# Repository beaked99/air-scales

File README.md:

Seth - everything for the KiCad is in the /hardware page. the project *should* open up at /hardware/air-scales. let me know if it doesnt work for you. At this stage all that is there is a big schematic, and ya... i went outside the fucking page border because i dont know how to update that either. fml. 
Scope of the project is to take an ESP32 run it off 12V vehicle power, read 0-5V air pressure on the ESP32. read ambient air pressure and ambient air temperature. Add GPS sensor if I can to get LAT / LONG. ESP32 should only have a headache rack connecting outside 12V power and the main 0-5V air pressure. 
I haven't decided what air pressure sensor I will use. I might look long and hard at the competitors link you sent me to see what they are using. I dont think I want battery power unlike them, no truck driver wants to hop in their semi and not see the fucking esp32 cause some stupid battery went dead. super easy to hook into trailer light wiring at the very least. we are not pulling a lot of watts here on this whole operation I dont think.

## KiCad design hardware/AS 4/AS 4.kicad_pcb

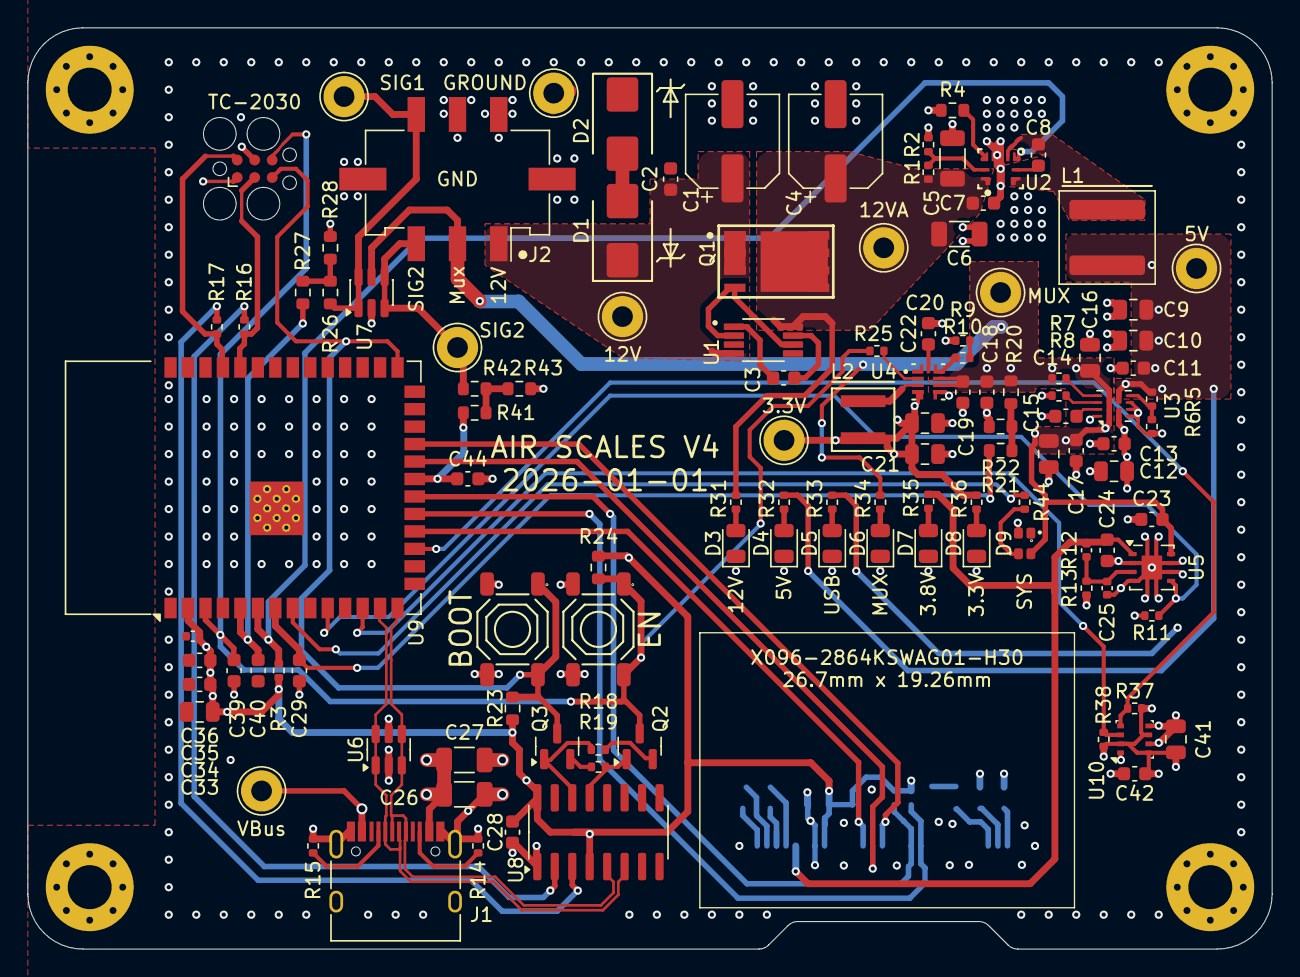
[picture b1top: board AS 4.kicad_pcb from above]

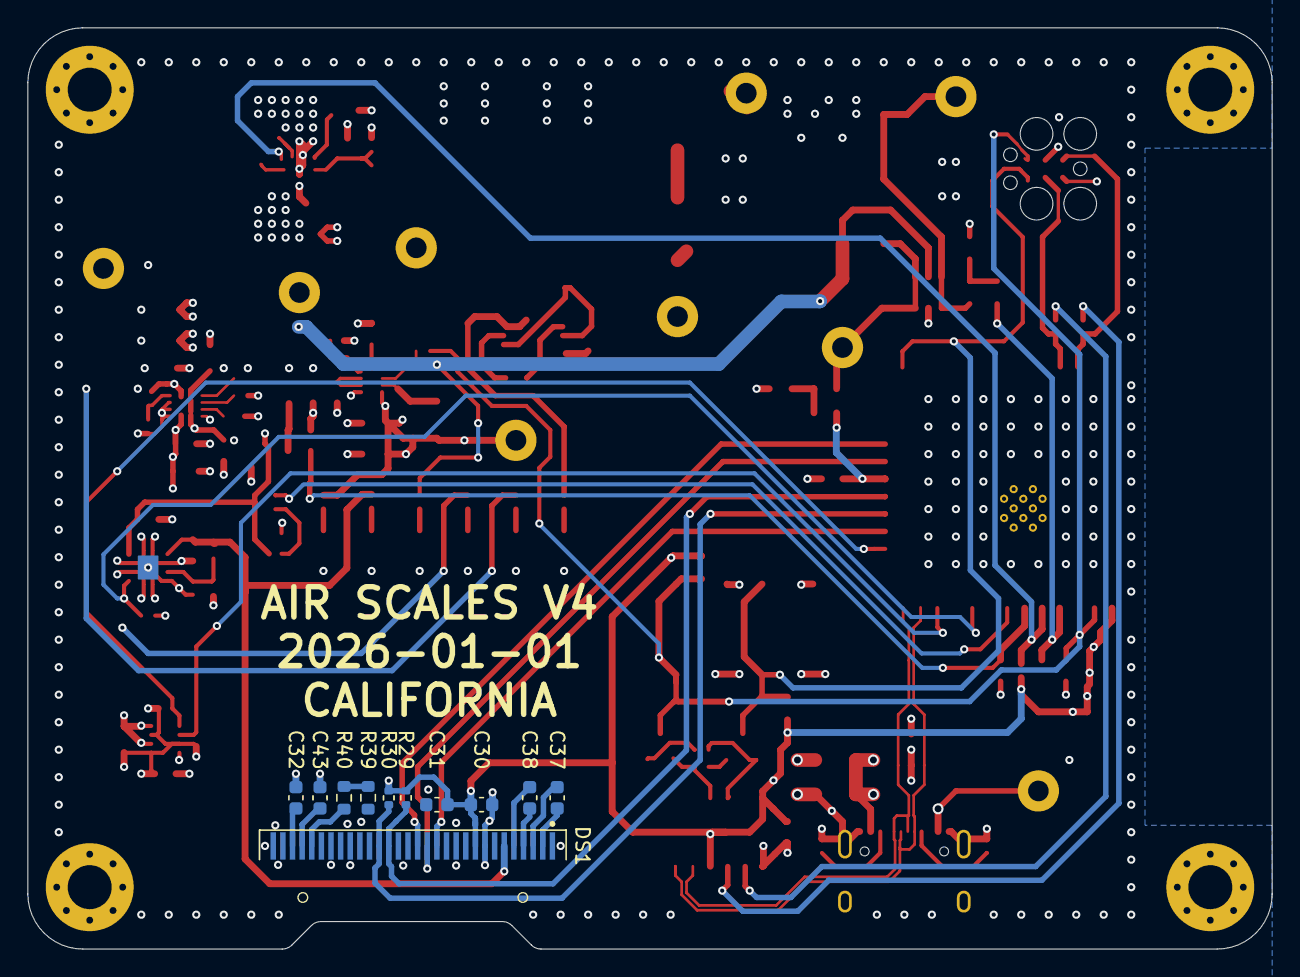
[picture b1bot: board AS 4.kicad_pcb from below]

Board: 4 copper layers, 90.5 x 67.0 mm, 131 parts (11 on the bottom side), 73 nets.

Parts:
C1, C4: 47uF; CP_Elec_6.3x7.7
C2, C7, C8, C11, C13, C14, C17, C18, C19, C28, C29, C30, C31, C34, C35, C37, C38, C40, C42, C44: 100nF; C_0603_1608Metric
C3, C23, C24, C32: 2.2uF; C_0603_1608Metric
C5, C6: 10uF; C_1206_3216Metric
C9, C15, C16, C20, C21: 22uF; C_0805_2012Metric
C10, C12, C33, C41: 10uF; C_0805_2012Metric
C22: 22nF; C_0603_1608Metric
C25, C36: 10nF; C_0402_1005Metric
C26, C27: 22uF; C_1206_3216Metric
C39: 1uF; C_0603_1608Metric
C43: 4.7uF; C_0603_1608Metric
D1: SMBJ28A; D_SMB
D2: SMBJ14A; D_SMB
D3, D4, D5, D6, D7, D8: LED_Small; LED_0805_2012Metric
D9: WS2812B; LED-SMD_4P-L1.6-W1.5_XL-1615RGBC-WS2812B
DS1: OLED-128O064D
H1, H2, H3, H4: MountingHole_Pad; MountingHole_3.2mm_M3_Pad_Via
J1: USB_C_Receptacle_USB2.0_16P; USB_C_Receptacle_HRO_TYPE-C-31-M-12
J2: Conn_02x03_Odd_Even; Molex_Micro-Fit_3.0_43045-0618_2x03-1MP_P3.00mm_Vertical
J3: TC2030-NL; Tag-Connect_TC2030-IDC-FP_2x03_P1.27mm_Vertical
L1: 10uH; L_Coilcraft_XAL6060-XXX
L2: 2.2uH; IND_XGL4020_COC
Q1: IAUC120N06S5L011; INF-PG-TDSON-8-33-V
Q2, Q3: S8050; SOT-23
R1, R11: 100K; R_0402_1005Metric
R2, R10: 15K; R_0402_1005Metric
R3, R5, R7, R13, R18, R19, R25: 10K; R_0402_1005Metric
R4: 82K; R_0603_1608Metric
R6, R29, R30, R31: 4.7K; R_0402_1005Metric
R8: 82K; R_0402_1005Metric
R9: 47K; R_0402_1005Metric
R12: 22K; C_0402_1005Metric
R14, R15: 5.1K; R_0402_1005Metric
R16, R17, R32, R33, R34, R37, R38: 1K; R_0402_1005Metric
R20, R26, R41: 68K; R_0603_1608Metric
R21, R27, R42: 220; R_0603_1608Metric
R22, R23, R24, R28, R43: 100K; R_0603_1608Metric
R35: 500; R_0402_1005Metric
R36, R44: 220; R_0402_1005Metric
R39, R40: 300K; R_0603_1608Metric
S1, S2: Tactile Button, 160gf; SW-SMD_4P-L5.1-W5.1-P3.70-LS6.5-TL-2
TP1, TP2, TP3, TP4, TP5, TP6, TP7, TP8, TP9: TestPoint_Probe; TestPoint_THTPad_D3.0mm_Drill1.5mm
U1: LM74610QDGKTQ1; SOP65P490X110-8N
U2: LMR604205SRAKRQ1; RAK0009A-MFG
U3: TPS2121RUXR; Texas_VQFN-HR-12_2x2.5mm_P0.5mm
U4: TPS62901Q1; VQFNHR9_RYT_TEX
U5: TPS73501DRBR; Texas_DRB0008A
U6, U7: USBLC6-2SC6; SOT-23-6
U8: CH340C; SOP-16_3.9x9.9mm_P1.27mm
U9: ESP32-S3-WROOM-1
U10: BME280; Bosch_LGA-8_2.5x2.5mm_P0.65mm_ClockwisePinNumbering

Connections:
+3.3V: C20.1, C21.1, C28.1, C30.1, C31.1, C33.1, C34.1, C35.1, C36.1, C41.1, C42.1, DS1.9 (VDD), L2.2, R3.2, R23.2, R24.2, R29.1, R30.1, R36.1, R37.1, R38.1, TP5.1, U4.3 (VOS), U8.4 (V3), U8.16 (VCC), U9.2 (3V3), U10.2 (CSB), U10.6 (VDDIO), U10.8 (VDD)
+3.8V: C24.1, DS1.6 (VBAT), R12.1, R35.1, U5.1 (OUT)
+5V: C9.1, C10.1, C11.1, L1.2, R5.2, R32.1, TP3.1, U3.7 (IN1)
+5VBus: C12.1, C13.1, C26.1, C27.1, J1.A4 (VBUS), J1.A9 (VBUS), J1.B4 (VBUS), J1.B9 (VBUS), J3.1 (VCC), R33.1, TP6.1, U3.2 (IN2), U6.5 (VBUS)
+5VMUX: C15.1, C16.1, C17.1, C18.1, C19.1, C23.1, D9.2 (VDD), J2.2, R7.2, R20.2, R34.1, TP4.1, U3.1 (OUT), U3.8 (OUT__2), U4.5 (EN), U4.6 (VIN), U5.8 (IN), U7.5 (VBUS)
+12V: C1.1, C2.1, D1.1, J2.1, Q1.1 (SOURCE), Q1.2 (SOURCE), Q1.3 (SOURCE), TP1.1, U1.4 (ANODE)
+12VA: C4.1, C5.1, C6.1, C7.1, Q1.5 (DRAIN), Q1.6 (DRAIN), Q1.7 (DRAIN), Q1.8 (DRAIN), R1.1, R31.1, TP2.1, U1.8 (CATHODE), U2.1 (VIN)
/3.8VEN: R11.1, U5.5 (EN), U9.10 (IO17)
/5VNet: C8.2, L1.1, U2.3 (SW), U2.6 (FB)
/5VPG: R3.1, U2.5 (PG), U9.6 (IO6)
/5V_MUX_GPIO: C29.1, R21.1, U9.7 (IO7)
/BOOT: J3.5 (RST), Q3.3 (C), R23.1, S2.1 (A), S2.2 (B), U9.27 (IO0)
/CS: DS1.13 (~CS), U9.18 (IO10)
/D/C: DS1.15 (D/~C), U9.23 (IO21)
/EN: C39.1, J3.6 (BOOT), Q2.3 (C), R24.1, R25.1, S1.1 (A), S1.2 (B), U9.3 (EN)
/GATE: Q1.4 (GATE), U1.2 (GATEPULLDOWN), U1.6 (GATEDRIVE)
/LED: R44.1, U9.8 (IO15)
/MIP_1: J2.6, R26.2, TP8.1, U7.1 (I/O1), U7.6 (I/O1)
/MIP_2: J2.3, R41.2, TP9.1, U7.3 (I/O2), U7.4 (I/O2)
/PG: R25.2, U4.1 (PG)
/RES: DS1.14 (~RES), U9.22 (IO14)
/RXD0: J3.3 (RX), R16.1, U9.36 (RXD0)
/SCL: R37.2, U9.17 (IO9), U10.4 (SCK)
/SCLK: DS1.18 (D0), R29.2, U9.20 (IO12)
/SDA: R38.2, U9.12 (IO8), U10.3 (SDI)
/SDIN: DS1.19 (D1), R30.2, U9.19 (IO11)
/SIG_1: C40.1, R27.1, U9.5 (IO5)
/SIG_2: C44.1, R42.1, U9.21 (IO13)
/TXD0: J3.2 (TX), R17.1, U9.37 (TXD0)
/USB_D+: J1.A6 (D+), J1.B6 (D+), U6.3 (I/O2), U6.4 (I/O2), U8.5 (UD+), U9.14 (USB_D+)
/USB_D-: J1.A7 (D-), J1.B7 (D-), U6.1 (I/O1), U6.6 (I/O1), U8.6 (UD-), U9.13 (USB_D-)
GND: C1.2, C2.2, C4.2, C5.2, C6.2, C7.2, C9.2, C10.2, C11.2, C12.2, C13.2, C14.2, C15.2, C16.2, C17.2, C18.2, C19.2, C20.2, C21.2, C22.2, C23.2, C24.2, C25.2, C26.2, C27.2, C28.2, C29.2, C30.2, C31.2, C32.2, C33.2, C34.2, C35.2, C36.2, C39.2, C40.2, C41.2, C42.2, C43.1, C44.2, D2.1, D3.1 (K), D4.1 (K), D5.1 (K), D6.1 (K), D7.1 (K), D8.1 (K), D9.3 (GND), DS1.1 (GND), DS1.8 (VSS), DS1.10 (BS0), DS1.11 (BS1), DS1.12 (BS2), DS1.16 (R/~W), DS1.17 (E/~RD), DS1.21 (D3), DS1.22 (D4), DS1.23 (D5), DS1.24 (D6), DS1.25 (D7), DS1.29 (VLSS), DS1.30 (GND), H1.1, H2.1, H3.1, H4.1, J1.A1 (GND), J1.A12 (GND), J1.B1 (GND), J1.B12 (GND), J1.S1 (SHIELD), J2.4, J2.5, J2.MP (MountPin), J3.4 (GND), R2.2, R4.2, R6.1, R8.2, R10.2, R11.2, R13.2, R14.2, R15.2, R22.1, R28.1, R39.1, R43.1, S1.3 (C), S1.4 (D), S2.3 (C), S2.4 (D), TP7.1, U2.2 (PGND), U2.7 (MODE_SYNC), U3.3 (CP2), U3.4 (OV2), U3.5 (OV1), U3.12 (GND), U4.4 (GND), U5.2 (NC_1), U5.4 (GND), U5.6 (NC_2), U5.7 (NC_3), U5.9 (EP_1), U6.2 (GND), U7.2 (GND), U8.1 (GND), U9.1 (GND), U9.40 (GND), U9.41 (GND), U10.1 (GND), U10.5 (SDO), U10.7 (GND)
unnamed: D1.2, D2.2
unnamed: D3.2 (A), R31.2
unnamed: D4.2 (A), R32.2
unnamed: D5.2 (A), R33.2
unnamed: D6.2 (A), R34.2
unnamed: D7.2 (A), R35.2
unnamed: D8.2 (A), R36.2
unnamed: D9.4 (DIN), R44.2
unnamed: C38.2, DS1.5 (C1N)
unnamed: C38.1, DS1.4 (C1P)
unnamed: C37.1, DS1.2 (C2N)
unnamed: C37.2, DS1.3 (C2P)
unnamed: DS1.26 (IREF), R40.2
unnamed: C32.1, DS1.28 (VCC)
unnamed: C43.2, DS1.27 (VCOMH)
unnamed: J1.A5 (CC1), R15.1
unnamed: J1.B5 (CC2), R14.1
unnamed: Q2.2 (B), R18.1
unnamed: Q2.1 (E), R19.2, U8.13 (~DTR)
unnamed: Q3.2 (B), R19.1
unnamed: Q3.1 (E), R18.2, U8.14 (~RTS)
unnamed: R9.2, R10.1
unnamed: R20.1, R21.2, R22.2
unnamed: R26.1, R27.2, R28.2
unnamed: R39.2, R40.1
unnamed: R41.1, R42.2, R43.2
unnamed: C3.1, U1.7 (VCAPH)
unnamed: C3.2, U1.1 (VCAPL)
unnamed: C8.1, U2.4 (BOOT)
unnamed: R1.2, R2.1, U2.9 (EN)
unnamed: R4.1, U2.8 (RT)
unnamed: R8.1, U3.10 (ILIM)
unnamed: R5.1, R6.2, U3.6 (PR1)
unnamed: C14.1, U3.11 (SS)
unnamed: R7.1, U3.9 (ST)
unnamed: R9.1, U4.7 (MODE/S-CONF)
unnamed: C22.1, U4.8 (SS/TR)
unnamed: L2.1, U4.2 (SW)
unnamed: C25.1, R12.2, R13.1, U5.3 (FBNR)
unnamed: R17.2, U8.3 (RXD)
unnamed: R16.2, U8.2 (TXD)

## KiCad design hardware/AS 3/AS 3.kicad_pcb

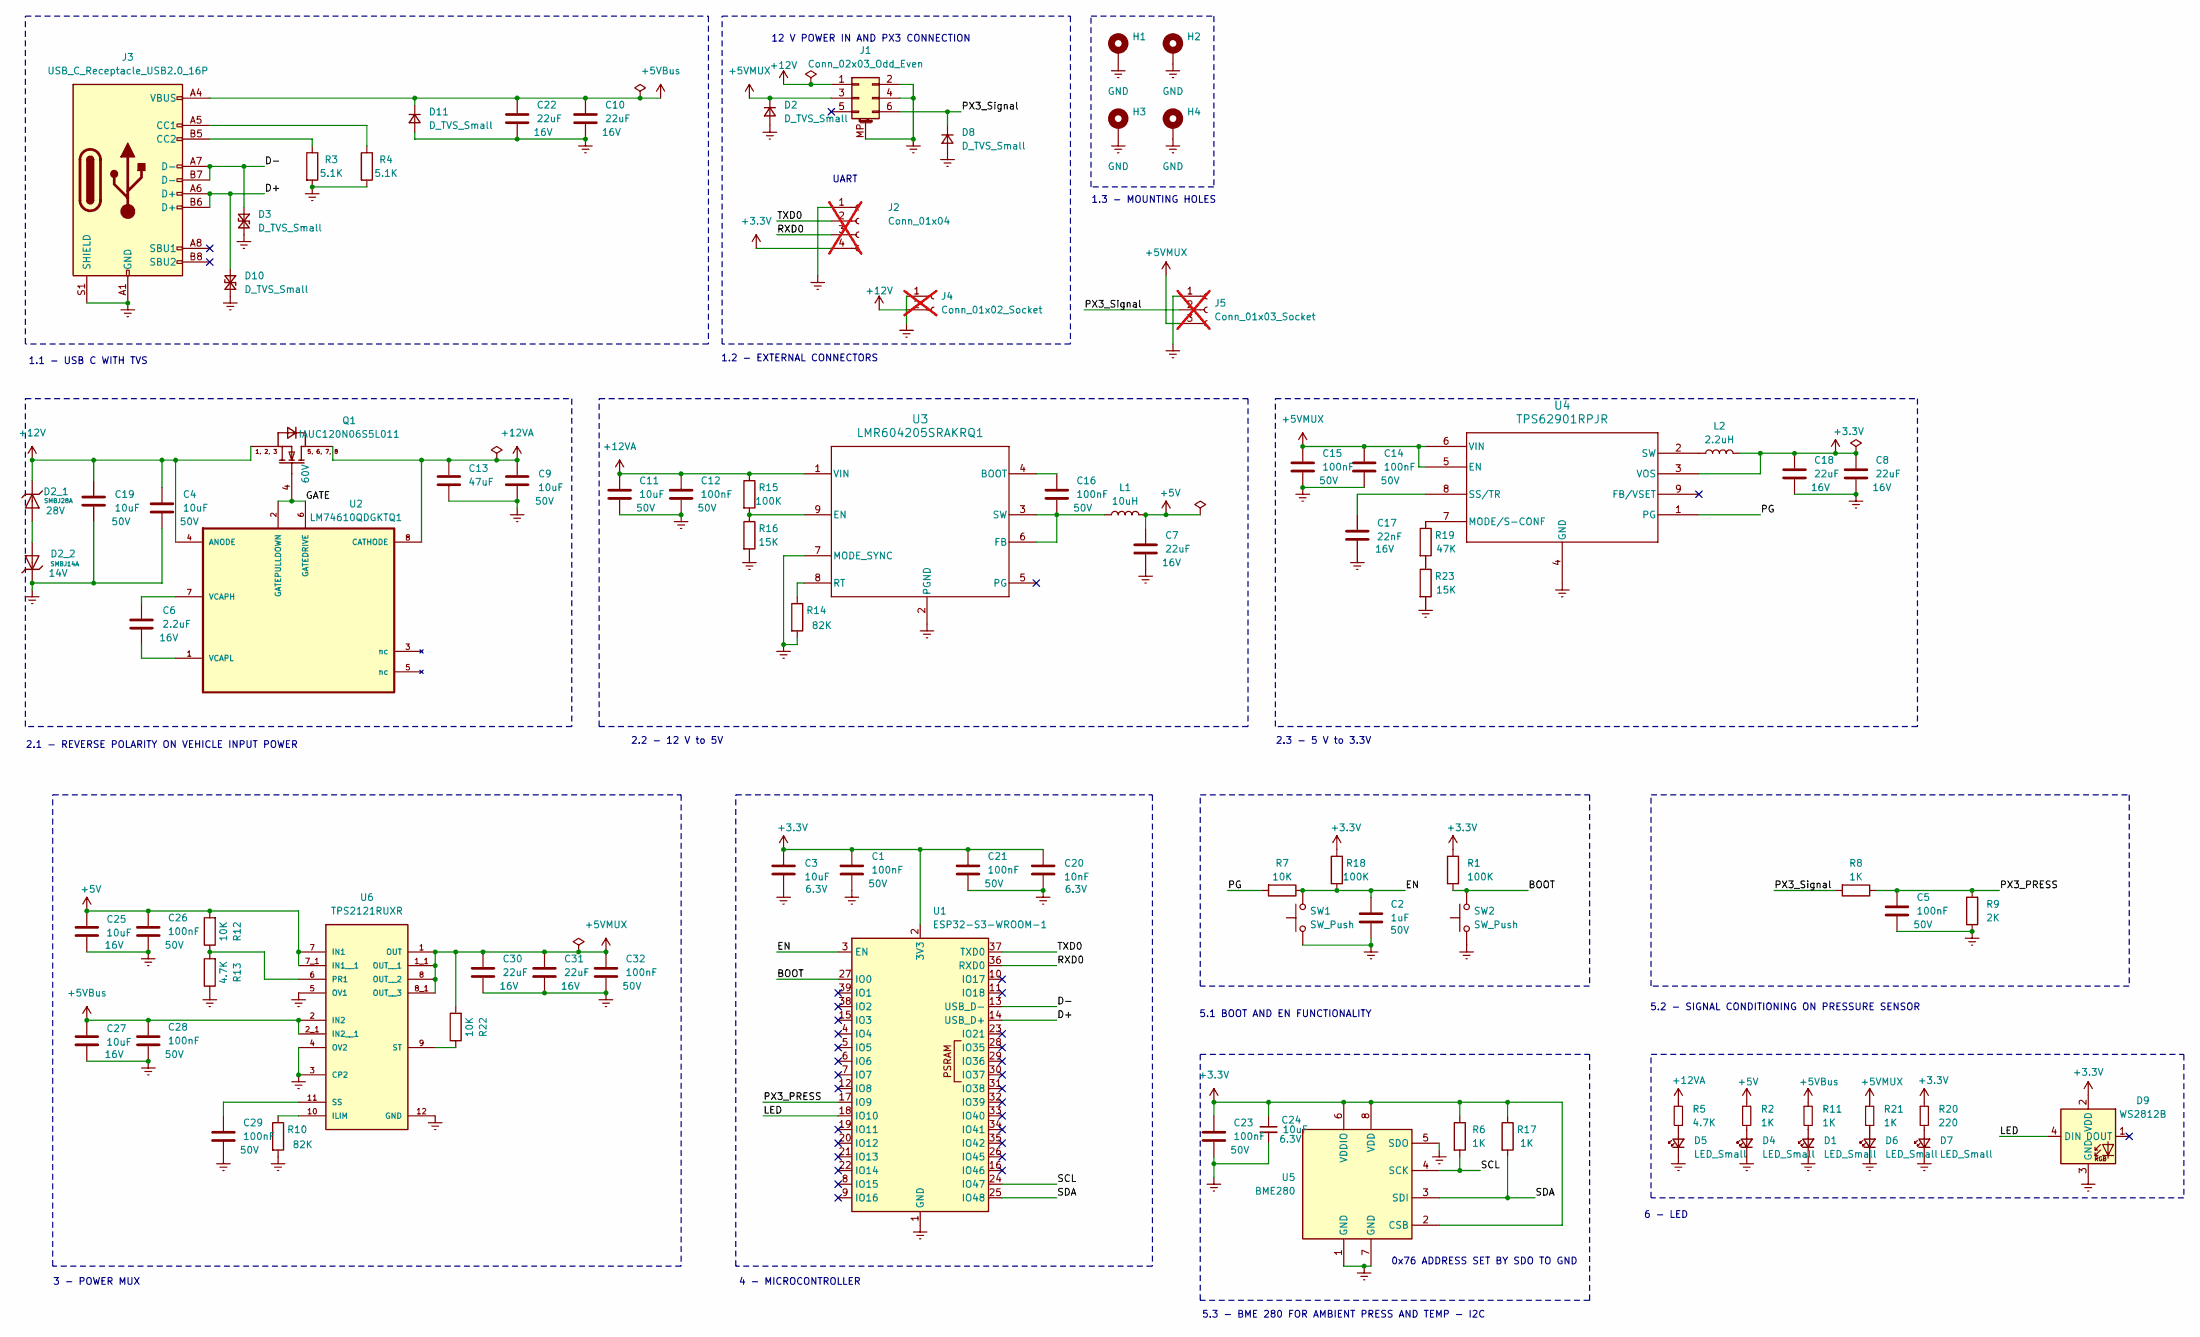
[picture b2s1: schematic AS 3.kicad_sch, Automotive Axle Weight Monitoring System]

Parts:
C1, C5, C12, C14, C15, C16, C21, C26, C28, C29, C32: 100nF; C_0603_1608Metric; Voltage 50V; Mfr. Part # CC0603KRX7R9BB104; LCSC C14663
C2: 1uF; C_0603_1608Metric; Voltage 50V; Mfr. Part # CL10A105KB8NNNC; LCSC C15849
C3: 10uF; C_0805_2012Metric; Voltage 6.3V
C4, C19: 10uF; C_0805_2012Metric; Voltage 50V; LCSC C440198
C6: 2.2uF; C_0603_1608Metric; Voltage 16V; Mfr. Part # CL10A225KO8NNNC; LCSC C23630
C7: 22uF; C_0805_2012Metric; Voltage 16V; Mfr. Part # CL21A226MAQNNNE; LCSC C45783
C8: 22uF; C_0805_2012Metric; Voltage 16V; LCSC C45783
C9: 10uF; C_1206_3216Metric; Voltage 50V; LCSC C13585
C10, C22: 22uF; C_1206_3216Metric; Voltage 16V; LCSC C12891
C11: 10uF; C_1206_3216Metric; Voltage 50V; Mfr. Part # CL31B106KBHNNNE; LCSC C89632
C13: 47uF; CP_Elec_6.3x7.7; Mfr. Part # VUP470M1HTR-0607; LCSC C28580967
C17: 22nF; C_0603_1608Metric; Voltage 16V; LCSC C21122
C18, C31: 22uF; C_0805_2012Metric; Voltage 16V; Mfr. Part # CL21A226MOCLRNC; LCSC C398815
C20: 10nF; C_0402_1005Metric; Voltage 6.3V; LCSC C15195
C23: 100nF; C_0603_1608Metric; Voltage 50V; Mfr. Part # GCM188R71H104KA57D; LCSC C85864
C24: 10uF; C_0805_2012Metric; Voltage 6.3V; LCSC C440198
C25, C27: 10uF; C_0805_2012Metric; Voltage 16V
C30: 22uF; C_0805_2012Metric; Voltage 16V; Mfr. Part # CL21A226MOCLRNC; LCSC C1729
D1, D5, D6, D7: LED_Small; LED_0805_2012Metric; JLCPCB Part No. C2297
D2, D8, D11: D_TVS_Small; D_SOD-882; Mfr. Part # SP1003-01ETG; LCSC C207270
D2_1: SMBJ28A; D_SMB; Voltage 28V; Clamping Voltage 45.4V; Mfr. Part # S-SMBJ28A; LCSC C19077582
D2_2: SMBJ14A; D_SMB; Voltage 14V; Mfr. Part # SMBJ14A; LCSC C908795
D3, D10: D_TVS_Small; D_SOD-882; Mfr. Part # SP3021-01ETG; LCSC C126839
D4: LED_Small; LED_0805_2012Metric; Mfr. Part # 19-219/GHC-YR2T1B5Y/3T; JLCPCB Part No. C2297
D9: WS2812B; LED-SMD_4P-L1.6-W1.5_XL-1615RGBC-WS2812B; Mfr. Part # XL-1615RGBC-2812B; LCSC C5349954
H1, H2, H3, H4: MountingHole_Pad; MountingHole_3.2mm_M3_DIN965_Pad_TopBottom
J1: Conn_02x03_Odd_Even; Molex_Micro-Fit_3.0_43045-0618_2x03-1MP_P3.00mm_Vertical; Mfr. Part # 430450618; LCSC C240837
J2: Conn_01x04; PinHeader_1x04_P1.00mm_Vertical; not fitted
J3: USB_C_Receptacle_USB2.0_16P; USB_C_Receptacle_HRO_TYPE-C-31-M-12; LCSC C165948
J4: Conn_01x02_Socket; PinHeader_1x02_P1.00mm_Vertical; not fitted
J5: Conn_01x03_Socket; PinHeader_1x03_P1.00mm_Vertical; not fitted
L1: 10uH; L_Chilisin_BMRF00101040; Mfr. Part # AMRU00101040100MA1; LCSC C6860374
L2: 2.2uH; IND_XGL6060_COC; Mfr. Part # XGL6060-222MEC; LCSC C3911671
Q1: IAUC120N06S5L011; INF-PG-TDSON-8-33-V; Voltage 60V; Mfr. Part # IAUC120N06S5L011ATMA1; LCSC C20190977
R1, R15, R18: 100K; R_0402_1005Metric
R2, R6, R11, R17, R21: 1K; R_0402_1005Metric; LCSC C11702
R3, R4: 5.1K; R_0402_1005Metric
R5, R13: 4.7K; R_0402_1005Metric
R7, R12, R22: 10K; R_0402_1005Metric
R8: 1K; R_0603_1608Metric
R9: 2K; R_0402_1005Metric
R10: 82K; R_0402_1005Metric
R14: 82K; R_0603_1608Metric; LCSC C23254
R16, R23: 15K; R_0402_1005Metric
R19: 47K; R_0402_1005Metric
R20: 220; R_0402_1005Metric
SW1, SW2: SW_Push; SW_SPST_Omron_B3FS-100xP
U1: ESP32-S3-WROOM-1; Mfr. Part # ESP32-S3-WROOM-1-N16R8; LCSC C2913202
U2: LM74610QDGKTQ1; SOP65P490X110-8N; Mfr. Part # LM74610QDGKTQ1; LCSC C202259
U3: LMR604205SRAKRQ1; RAK0009A-MFG; Mfr. Part # LMR604205SRAKRQ1; LCSC C51940365
U4: TPS62901RPJR; QFN_902RPJR_TEX
U5: BME280; Bosch_LGA-8_2.5x2.5mm_P0.65mm_ClockwisePinNumbering
U6: TPS2121RUXR; IC_TPS2121RUXR; LCSC C485916

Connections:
+3.3V: C1.1, C3.1, C8.1, C18.1, C20.1, C21.1, C23.1, C24.1, D9.2 (VDD), J2.4, L2.2, R1.1, R6.1, R17.1, R18.1, R20.1, U1.2 (3V3), U4.3 (VOS), U5.2 (CSB), U5.6 (VDDIO), U5.8 (VDD)
+5V: C7.1, C25.1, C26.1, L1.2, R2.1, R12.2, U6.7 (IN1), U6.7_1 (IN1__1)
+5VBus: C10.1, C22.1, C27.1, C28.1, D11.1 (K), J3.A4 (VBUS), J3.A9 (VBUS), J3.B4 (VBUS), J3.B9 (VBUS), R11.1, U6.2 (IN2), U6.2_1 (IN2__1)
+5VMUX: C14.1, C15.1, C30.1, C31.1, C32.1, D2.1 (K), J1.3, J5.3, R21.1, R22.2, U4.5 (EN), U4.6 (VIN), U6.1 (OUT), U6.1_1 (OUT__1), U6.8 (OUT__2), U6.8_1 (OUT__3)
+12V: C4.1, C19.1, D2_1.1, J1.1, J4.2, Q1.1 (SOURCE), Q1.2 (SOURCE), Q1.3 (SOURCE), U2.4 (ANODE)
+12VA: C9.1, C11.1, C12.1, C13.1, Q1.5 (DRAIN), Q1.6 (DRAIN), Q1.7 (DRAIN), Q1.8 (DRAIN), R5.1, R15.1, U2.8 (CATHODE), U3.1 (VIN)
/BOOT: R1.2, SW2.2, U1.27 (IO0)
/D+: D10.1 (A1), J3.A6 (D+), J3.B6 (D+), U1.14 (USB_D+)
/D-: D3.1 (A1), J3.A7 (D-), J3.B7 (D-), U1.13 (USB_D-)
/EN: C2.1, R7.1, R18.2, SW1.2, U1.3 (EN)
/GATE: Q1.4 (GATE), U2.2 (GATEPULLDOWN), U2.6 (GATEDRIVE)
/LED: D9.4 (DIN), U1.18 (IO10)
/PG: R7.2, U4.1 (PG)
/PX3_PRESS: C5.1, R8.1, R9.2, U1.17 (IO9)
/PX3_Signal: D8.1 (K), J1.6, J5.2, R8.2
/RXD0: J2.3, U1.36 (RXD0)
/SCL: R6.2, U1.24 (IO47), U5.4 (SCK)
/SDA: R17.2, U1.25 (IO48), U5.3 (SDI)
/TXD0: J2.2, U1.37 (TXD0)
GND: C1.2, C2.2, C3.2, C4.2, C5.2, C7.2, C8.2, C9.2, C10.2, C11.2, C12.2, C13.2, C14.2, C15.2, C17.2, C18.2, C19.2, C20.2, C21.2, C22.2, C23.2, C24.2, C25.2, C26.2, C27.2, C28.2, C29.2, C30.2, C31.2, C32.2, D1.1 (K), D2.2 (A), D2_2.1, D3.2 (A2), D4.1 (K), D5.1 (K), D6.1 (K), D7.1 (K), D8.2 (A), D9.3 (GND), D10.2 (A2), D11.2 (A), H1.1, H2.1, H3.1, H4.1, J1.2, J1.4, J1.MP (MountPin), J2.1, J3.A1 (GND), J3.A12 (GND), J3.B1 (GND), J3.B12 (GND), J3.S1 (SHIELD), J4.1, J5.1, R3.2, R4.2, R9.1, R10.2, R13.1, R14.2, R16.2, R23.2, SW1.1, SW2.1, U1.1 (GND), U1.40 (GND), U1.41 (GND), U3.2 (PGND), U3.7 (MODE_SYNC), U4.4 (GND), U5.1 (GND), U5.5 (SDO), U5.7 (GND), U6.3 (CP2), U6.4 (OV2), U6.5 (OV1), U6.12 (GND)
unnamed: D1.2 (A), R11.2
unnamed: D2_1.2, D2_2.2
unnamed: D4.2 (A), R2.2
unnamed: D5.2 (A), R5.2
unnamed: D6.2 (A), R21.2
unnamed: D7.2 (A), R20.2
unnamed: J3.A5 (CC1), R4.1
unnamed: J3.B5 (CC2), R3.1
unnamed: R19.2, R23.1
unnamed: C6.1, U2.7 (VCAPH)
unnamed: C6.2, U2.1 (VCAPL)
unnamed: C16.1, U3.4 (BOOT)
unnamed: R15.2, R16.1, U3.9 (EN)
unnamed: C16.2, L1.1, U3.3 (SW), U3.6 (FB)
unnamed: R14.1, U3.8 (RT)
unnamed: R19.1, U4.7 (MODE/S-CONF)
unnamed: C17.1, U4.8 (SS/TR)
unnamed: L2.1, U4.2 (SW)
unnamed: R10.1, U6.10 (ILIM)
unnamed: R12.1, R13.2, U6.6 (PR1)
unnamed: C29.1, U6.11 (SS)
unnamed: R22.1, U6.9 (ST)

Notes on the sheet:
5.1 BOOT AND EN FUNCTIONALITY
1.3 - MOUNTING HOLES
2.1 - REVERSE POLARITY ON VEHICLE INPUT POWER
3 - POWER MUX
UART
12 V POWER IN AND PX3 CONNECTION
1.2 - EXTERNAL CONNECTORS
5.3 - BME 280 FOR AMBIENT PRESS AND TEMP - I2C
4 - MICROCONTROLLER
1.1 - USB C WITH TVS
0x76 ADDRESS SET BY SDO TO GND
5.2 - SIGNAL CONDITIONING ON PRESSURE SENSOR
2.3 - 5 V to 3.3V
2.2 - 12 V to 5V
6 - LED

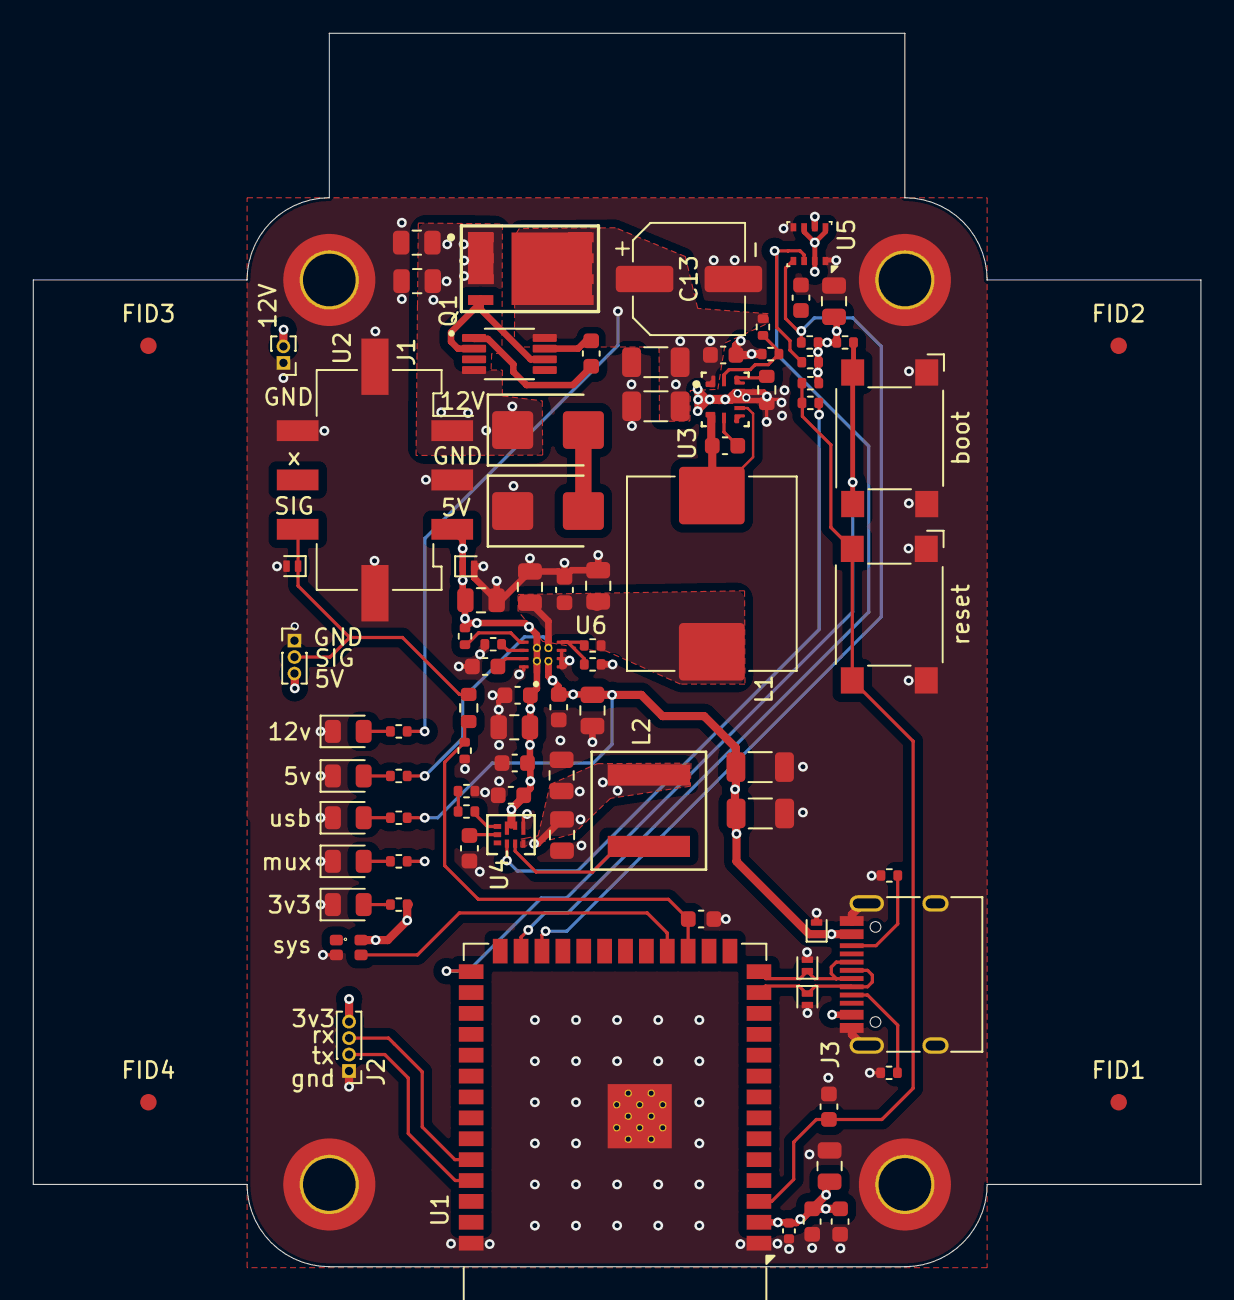
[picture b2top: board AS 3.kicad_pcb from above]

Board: 4 copper layers, 71.0 x 75.0 mm, 92 parts (0 on the bottom side), 42 nets.

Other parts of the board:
FID1, FID2, FID3, FID4: Fiducial; Fiducial_1mm_Mask2mm

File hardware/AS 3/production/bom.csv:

Designator,Footprint,Quantity,Value,LCSC Part #
"C1, C12, C14, C15, C16, C21, C26, C28, C29, C32, C5",0603,11,100nF,C14663
"C10, C22",1206,2,22uF,C12891
C11,1206,1,10uF,C89632
C13,CP_Elec_6.3x5.7,1,47uF,C3274488
C17,0603,1,22nF,C21122
"C18, C31",0805,2,22uF,C398815
"C19, C24, C4",0805,3,10uF,C440198
C2,0603,1,1uF,C15849
C20,0402,1,10nF, C15195
C23,0603,1,100nF,C85864
"C25, C27, C3",0805,3,10uF,
C30,0805,1,22uF,C1729
C6,0603,1,2.2uF, C23630
C7,0805,1,22uF, C45783
C8,0805,1,22uF,C45783
C9,1206,1,10uF, C13585
"D1, D4, D5, D6, D7",0805,5,LED_Small,C2297
"D10, D3",D_SOD-882,2,D_TVS_Small,C126839
"D11, D2, D8",D_SOD-882,3,D_TVS_Small,C207270
D2_1,D_SMB,1,SMBJ28A,C19077582
D2_2,D_SMB,1,SMBJ14A,C908795
D9,LED-SMD_4P-L1.6-W1.5_XL-1615RGBC-WS2812B,1,WS2812B,C5349954
J1,Molex_Micro-Fit_3.0_43045-0618_2x03-1MP_P3.00mm_Vertical,1,Conn_02x03_Odd_Even,C240837
J3,USB_C_Receptacle_HRO_TYPE-C-31-M-12,1,USB_C_Receptacle_USB2.0_16P,C165948
L1,L_Chilisin_BMRF00101040,1,10uH,C6860374
L2,IND_XGL6060_COC,1,2.2uH,C3911671
Q1,INF-PG-TDSON-8-33-V,1,IAUC120N06S5L011,C20190977
"R1, R15, R18",0402,3,100K,
R10,0402,1,82K,
"R11, R17, R2, R21, R6",0402,5,1K, C11702
"R12, R22, R7",0402,3,10K,
"R13, R5",0402,2,4.7K,
R14,0603,1,82K,C23254
"R16, R23",0402,2,15K,
R19,0402,1,47K,
R20,0402,1,220,
"R3, R4",0402,2,5.1K,
R8,0603,1,1K,
R9,0402,1,2K,
"SW1, SW2",SW_SPST_Omron_B3FS-100xP,2,SW_Push,
U1,ESP32-S3-WROOM-1,1,ESP32-S3-WROOM-1,C2913202
U2,SOP65P490X110-8N,1,LM74610QDGKTQ1,C202259
U3,RAK0009A-MFG,1,LMR604205SRAKRQ1,C51940365
U4,QFN_902RPJR_TEX,1,TPS62901RPJR,
U5,Bosch_LGA-8_2.5x2.5mm_P0.65mm_ClockwisePinNumbering,1,BME280,C92489
U6,IC_TPS2121RUXR,1,TPS2121RUXR, C485916
